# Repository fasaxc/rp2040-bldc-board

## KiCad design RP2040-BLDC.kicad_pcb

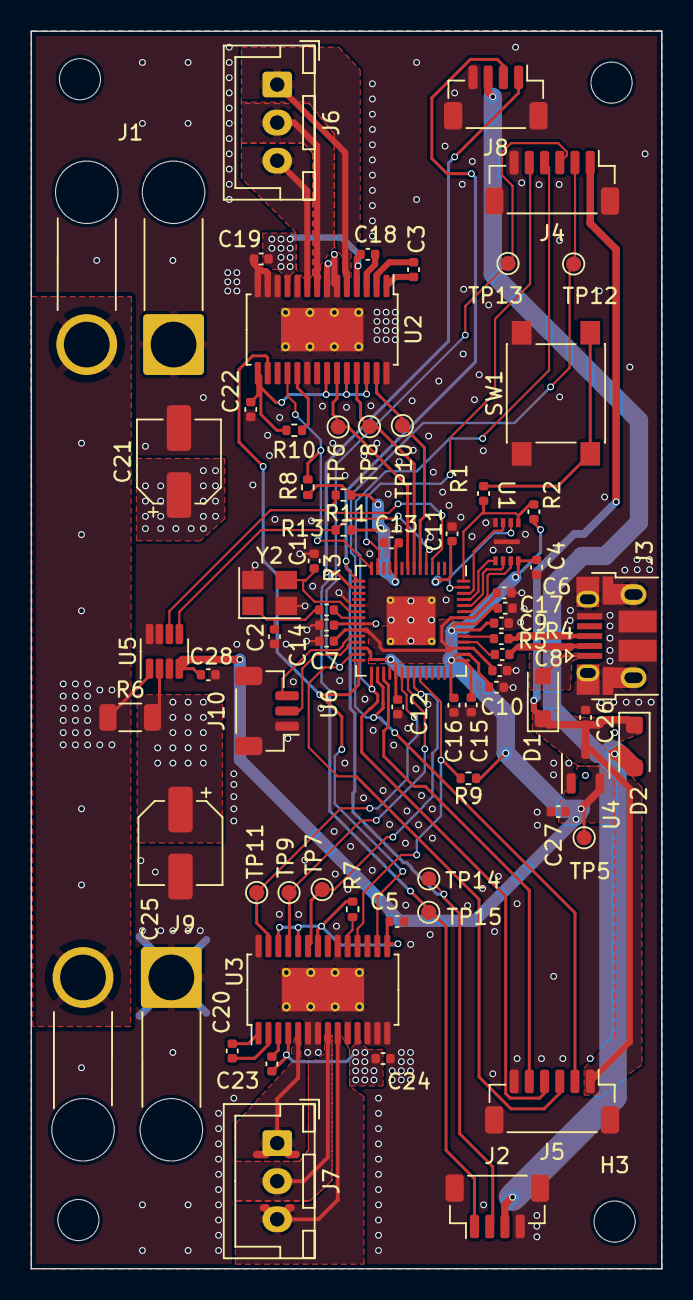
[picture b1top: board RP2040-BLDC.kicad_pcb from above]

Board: 4 copper layers, 41.4 x 81.2 mm, 75 parts (0 on the bottom side), 58 nets.

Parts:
C1, C2: 27p; C_0402_1005Metric
C3, C20: 0.01u; C_0402_1005Metric
C4, C6, C7, C9, C11, C12, C13, C14, C15, C16, C17: 100n; C_0402_1005Metric
C5, C22: 0.47u; C_0402_1005Metric
C8, C10, C26, C27: 1u; C_0402_1005Metric
C18, C19, C23, C24: 0.1u; C_0402_1005Metric
C21, C25: 100u; CP_Elec_5x5.4
C28: C_Small; C_0402_1005Metric
D1, D2: MBR1020VL; D_SOD-123F
H1, H2, H3, H4: MountingHole; MountingHole_2.7mm_M2.5
J1: MPWR; SolderWire-2.5sqmm_1x02_P7.2mm_D2.4mm_OD3.6mm_ShortRelief_F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
J2, J8: Conn_01x04_MountingPin; JST_SH_BM04B-SRSS-TB_1x04-1MP_P1.00mm_Vertical
J3: USB_B_Micro; USB_Micro-B_Amphenol_10103594-0001LF_Horizontal
J4, J5: Conn_01x06_MountingPin; JST_SH_BM06B-SRSS-TB_1x06-1MP_P1.00mm_Vertical
J6: M1; JST_XH_B3B-XH-A_1x03_P2.50mm_Vertical
J7: M2; JST_XH_B3B-XH-A_1x03_P2.50mm_Vertical
J9: MPWR; SolderWire-2.5sqmm_1x02_P7.2mm_D2.4mm_OD3.6mm_ShortRelief
J10: DBG; JST_SH_BM03B-SRSS-TB_1x03-1MP_P1.00mm_Vertical
R1, R3: 1k; C_0402_1005Metric
R2: DNF; C_0402_1005Metric
R4, R5: 27; C_0402_1005Metric
R6: 0.01; R_1206_3216Metric
R7, R8, R9, R10: 10k; R_0402_1005Metric
R11, R13: 2k; R_0402_1005Metric
SW1: Flash; SW_Push_1P1T_NO_6x6mm_H9.5mm
TP5, TP6, TP7, TP8, TP9, TP10, TP11, TP12, TP13, TP14, TP15: TestPoint_Small; TestPoint_Pad_D1.0mm
U1: USON 2x3mm
U2, U3: DRV8313; HTSSOP-28-1EP_4.4x9.7mm_P0.65mm_EP2.85x5.4mm_ThermalVias
U4: XC6206PxxxMR; SOT-23-3
U5: INA219AxDCN; SOT-23-8
U6: RP2040; QFN-56-1EP_7x7mm_P0.4mm_EP3.2x3.2mm_ThermalVias
Y2: 12MHz X322512MSB4SI; Crystal_SMD_3225-4Pin_3.2x2.5mm

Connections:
+1V1: C6.1, C7.1, C8.1, U6.23 (DVDD), U6.45 (VREG_VOUT), U6.50 (DVDD)
+3V3: C4.1, C9.1, C10.1, C11.1, C12.1, C13.1, C14.1, C15.1, C16.1, C17.1, C27.1, C28.1, R2.1, R8.1, R9.1, R11.1, R13.1, TP5.1, U1.8 (VCC), U4.2 (VO), U5.4 (VS), U6.1 (IOVDD), U6.10 (IOVDD), U6.22 (IOVDD), U6.26 (RUN), U6.33 (IOVDD), U6.42 (IOVDD), U6.43 (ADC_AVDD), U6.44 (VREG_IN), U6.48 (USB_VDD), U6.49 (IOVDD)
+5V: C26.1, D1.1 (K), D2.1 (K), J4.1, J5.1, U4.3 (VI)
+BATT: C18.1, C19.1, C21.1, C23.1, C24.1, C25.1, R6.2, U2.4 (VM), U2.11 (VM), U3.4 (VM), U3.11 (VM), U5.2 (IN-)
/DRV1FAULT: R8.2, U2.18 (~FAULT), U6.14 (GPIO11)
/DRV1IN1: TP10.1, U2.27 (IN1), U6.6 (GPIO4)
/DRV1IN2: TP8.1, U2.25 (IN2), U6.7 (GPIO5)
/DRV1IN3: TP6.1, U2.23 (IN3), U6.8 (GPIO6)
/DRV2FAULT: R9.2, U3.18 (~FAULT), U6.37 (GPIO25)
/DRV2IN1: TP11.1, U3.27 (IN1), U6.34 (GPIO22)
/DRV2IN2: TP9.1, U3.25 (IN2), U6.35 (GPIO23)
/DRV2IN3: TP7.1, U3.23 (IN3), U6.36 (GPIO24)
/DRV~RESET: U2.16 (~RESET), U3.16 (~RESET), U6.28 (GPIO17)
/Driver sensor pair1/DRV3.3VOUT: C5.1, R7.2, U3.15 (V3P3), U3.22 (EN3), U3.24 (EN2), U3.26 (EN1)
/Driver sensor pair1/MA: J7.1, U3.5 (OUT1)
/Driver sensor pair1/MB: J7.2, U3.8 (OUT2)
/Driver sensor pair1/MC: J7.3, U3.9 (OUT3)
/Driver sensor pair/DRV3.3VOUT: C22.1, R10.2, U2.15 (V3P3), U2.22 (EN3), U2.24 (EN2), U2.26 (EN1)
/Driver sensor pair/MA: J6.1, U2.5 (OUT1)
/Driver sensor pair/MB: J6.2, U2.8 (OUT2)
/Driver sensor pair/MC: J6.3, U2.9 (OUT3)
/I2C0_SCL: J2.1, J8.1, TP15.1, U6.16 (GPIO13)
/I2C0_SDA: J2.2, J8.2, TP14.1, U6.15 (GPIO12)
/I2C1SCL: R13.2, U5.5 (SCL), U6.5 (GPIO3)
/I2C1SDA: R11.2, U5.6 (SDA), U6.4 (GPIO2)
/QSPI_SCLK: U1.6 (CLK), U6.52 (QSPI_SCLK)
/QSPI_SD0: U1.5 (DI(IO0)), U6.53 (QSPI_SD0)
/QSPI_SD1: U1.2 (DO(IO1)), U6.55 (QSPI_SD1)
/QSPI_SD2: U1.3 (~WP(IO2)), U6.54 (QSPI_SD2)
/QSPI_SD3: U1.7 (~RESET(IO3)), U6.51 (QSPI_SD3)
/QSPI_SS: R1.1, R2.2, U1.1 (~CS), U6.56 (QSPI_SS)
/SEN1CS: J4.5, U6.13 (GPIO10)
/SEN2CS: J5.5, U6.31 (GPIO20)
/SPI0_RX: J4.3, J5.3, TP13.1, U6.27 (GPIO16)
/SPI0_SCK: J4.4, J5.4, U6.29 (GPIO18)
/SPI0_TX: J4.2, J5.2, TP12.1, U6.30 (GPIO19)
/SWCLK: J10.3, U6.24 (SWCLK)
/SWD: J10.2, U6.25 (SWD)
/USB_D+: J3.3 (D+), R4.1
/USB_D-: J3.2 (D-), R5.1
/XIN: C1.1, U6.20 (XIN), Y2.3
/XOUT: R3.1, U6.21 (XOUT)
/~USB_BOOT: R1.2, SW1.2
GND: C1.2, C2.2, C4.2, C5.2, C6.2, C7.2, C8.2, C9.2, C10.2, C11.2, C12.2, C13.2, C14.2, C15.2, C16.2, C17.2, C19.2, C21.2, C22.2, C24.2, C25.2, C26.2, C27.2, C28.2, J1.1, J2.4, J2.MP (MountPin), J3.5 (GND), J3.6 (Shield), J4.6, J4.MP (MountPin), J5.6, J5.MP (MountPin), J8.4, J8.MP (MountPin), J9.1, J10.1, J10.MP (MountPin), SW1.1, U1.4 (GND), U1.9 (PAD), U2.6 (PGND1), U2.7 (PGND2), U2.10 (PGND3), U2.12 (COMPP), U2.13 (COMPN), U2.14 (GND), U2.20 (GND), U2.28 (GND), U2.29 (PAD_GND), U3.6 (PGND1), U3.7 (PGND2), U3.10 (PGND3), U3.12 (COMPP), U3.13 (COMPN), U3.14 (GND), U3.20 (GND), U3.28 (GND), U3.29 (PAD_GND), U4.1 (GND), U5.3 (GND), U5.7 (A0), U5.8 (A1), U6.19 (TESTEN), U6.57 (GND), Y2.2, Y2.4
unnamed: C2.1, R3.2, Y2.1
unnamed: D2.2 (A), J2.3, J8.3
unnamed: J1.2, J9.2, R6.1, U5.1 (IN+)
unnamed: C3.2, U2.2 (CPH)
unnamed: C3.1, U2.1 (CPL)
unnamed: C18.2, U2.3 (VCP)
unnamed: R10.1, U2.19 (~COMPO)
unnamed: C20.2, U3.2 (CPH)
unnamed: C20.1, U3.1 (CPL)
unnamed: C23.2, U3.3 (VCP)
unnamed: R7.1, U3.19 (~COMPO)
unnamed: R5.2, U6.46 (USB_DM)
unnamed: R4.2, U6.47 (USB_DP)
VBUS: D1.2 (A), J3.1 (VBUS)

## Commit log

2023-11-14 Initial commit - partial schematic; round layout
2023-12-10 First pass at routing board.
    - Add INA219 current sensor and shunt
    - Route motor traces.
    - Still need to fix a few footprints.
2023-12-13 Make vias bigger
2023-12-13 Tweaks
